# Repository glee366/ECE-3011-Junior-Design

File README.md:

# ECE-3011-Junior-Design
Junior Design project

https://github.com/Ian-Boraks/ECE3011-STEAM/tree/Feedback

# About This Project

## 📚 Educational Gameboy using ESP32

This project showcases an **educational Gameboy** designed using the ESP32 microcontroller. The Gameboy integrates various peripherals and features to provide an engaging learning experience for students, focusing on math and music skills. 

## Key Features
- **Microcontroller**: ESP32 for efficient processing and Wi-Fi capabilities.
- **Display**: A colorful LCD screen to render interactive content.
- **Input**: Capacitive touch buttons and a navigation switch for user interaction.
- **Feedback Mechanisms**: Integrated speakers and haptic feedback for immersive learning.

## Highlights in Code

### 1. Display Initialization
The following code snippet demonstrates how the LCD display was initialized to render the game's user interface:

```cpp
#include <TFT_eSPI.h>

TFT_eSPI tft = TFT_eSPI(); // Initialize TFT library

void setupDisplay() {
    tft.init();
    tft.setRotation(1);
    tft.fillScreen(TFT_BLACK);
    tft.setTextColor(TFT_WHITE, TFT_BLACK); // Set text color
    tft.setTextDatum(MC_DATUM); // Center alignment
}
```

### 2. Sound Feedback
Using the ESP32's PWM capabilities, the speaker plays sound effects based on user input:

```cpp
void playTone(int frequency, int duration) {
    ledcAttachPin(10, 0); // Attach GPIO 10 to channel 0
    ledcWriteTone(0, frequency); // Set frequency
    delay(duration);
    ledcWriteTone(0, 0); // Stop sound
}
```

### 3. Tap Detection with the Microphone
The microphone setup detects tap events for input recognition:

```cpp
void detectTap() {
    int soundLevel = analogRead(A0);
    if (soundLevel > THRESHOLD) {
        Serial.println("Tap detected!");
    }
}
```

## Repository Structure
```plaintext
├── code/
│   ├── src/
│   │   ├── main.cpp       # Main program logic
│   │   ├── display.cpp    # Display handling code
│   │   ├── sound.cpp      # Sound feedback logic
│   │   ├── input.cpp      # User input processing
│   └── assets/
│       ├── icons/         # Game icons
│       └── sounds/        # Sound effects
└── README.md              # Project documentation
```

## Product Image

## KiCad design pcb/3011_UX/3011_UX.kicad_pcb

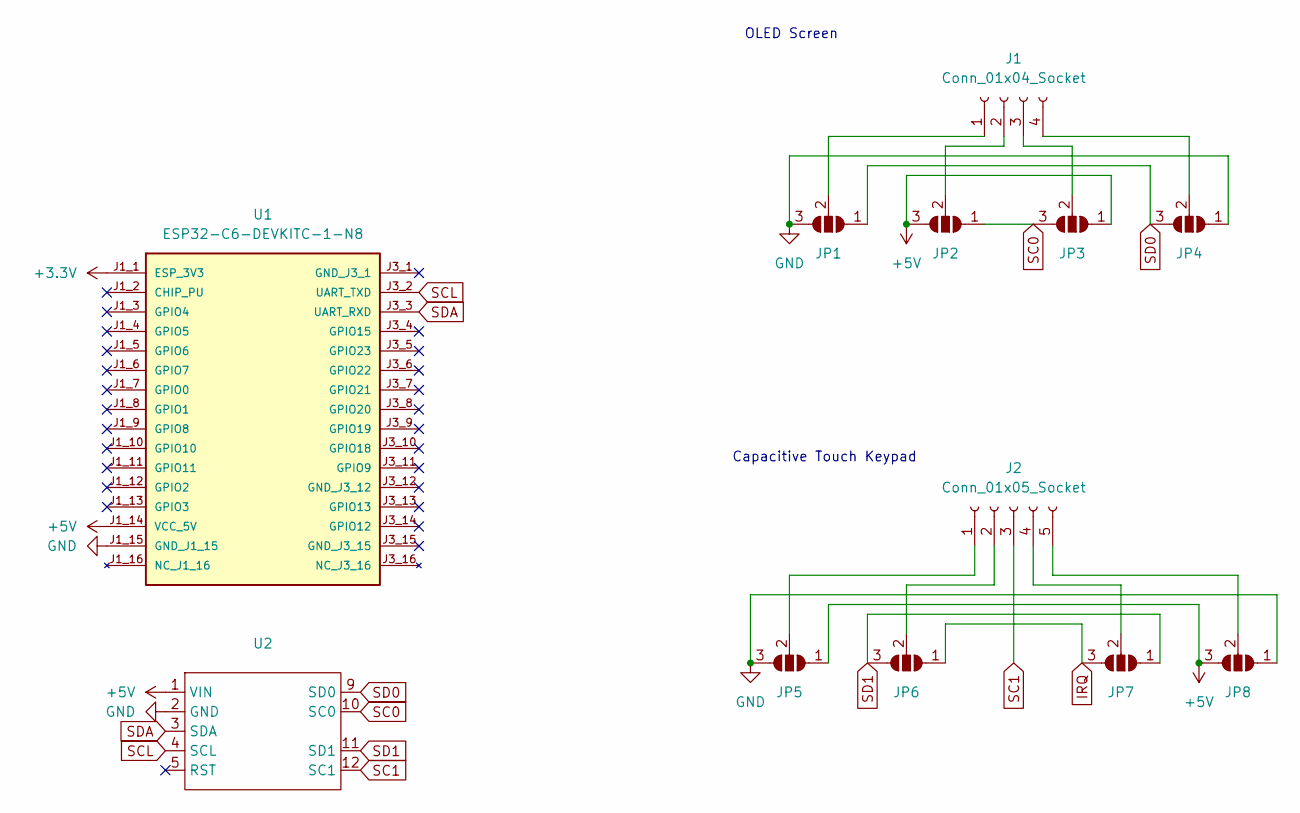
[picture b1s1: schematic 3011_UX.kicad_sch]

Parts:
J1: Conn_01x04_Socket; PinHeader_1x04_P2.54mm_Vertical
J2: Conn_01x05_Socket; PinHeader_1x05_P2.54mm_Vertical
JP1, JP2, JP3, JP4, JP5, JP6, JP7, JP8: SolderJumper_3_Open; SolderJumper-3_P1.3mm_Bridged2Bar12_RoundedPad1.0x1.5mm
U1: ESP32-C6-DEVKITC-1-N8; MODULE_ESP32-C6-DEVKITC-1-N8; PARTREV 1.3
U2: B0BFD4X6YV

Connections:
+3.3V: U1.J1_1 (ESP_3V3)
+5V: JP2.3 (B), JP3.1 (A), JP5.1 (A), JP8.3 (B), U1.J1_14 (VCC_5V), U2.1 (VIN)
GND: JP1.3 (B), JP4.1 (A), JP5.3 (B), JP8.1 (A), U1.J1_15 (GND_J1_15), U2.2 (GND)
IRQ: JP6.1 (A), JP7.3 (B)
unnamed: J1.1, JP1.2 (C)
unnamed: J1.2, JP2.2 (C)
unnamed: J1.3, JP3.2 (C)
unnamed: J1.4, JP4.2 (C)
unnamed: J2.1, JP5.2 (C)
unnamed: J2.2, JP6.2 (C)
unnamed: J2.4, JP7.2 (C)
unnamed: J2.5, JP8.2 (C)
RST: U2.5 (RST)
SC0: JP2.1 (A), JP3.3 (B), U2.10 (SC0)
SC1: J2.3, U2.12 (SC1)
SCL: U1.J3_2 (UART_TXD), U2.4 (SCL)
SD0: JP1.1 (A), JP4.3 (B), U2.9 (SD0)
SD1: JP6.3 (B), JP7.1 (A), U2.11 (SD1)
SDA: U1.J3_3 (UART_RXD), U2.3 (SDA)

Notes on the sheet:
OLED Screen
Capacitive Touch Keypad

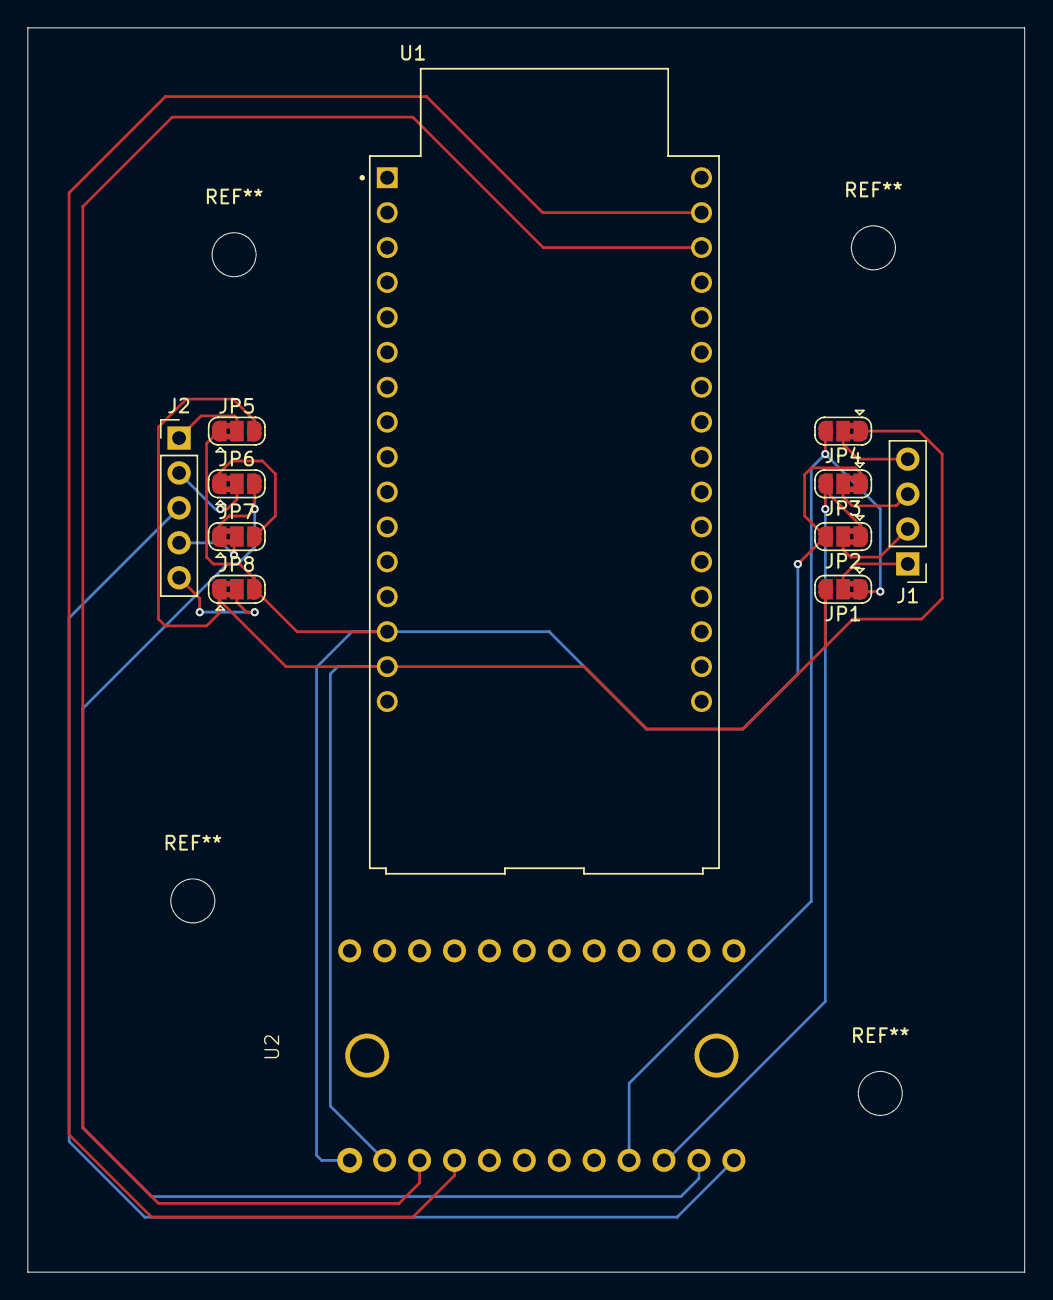
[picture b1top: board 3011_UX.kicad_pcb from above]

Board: 2 copper layers, 72.5 x 90.5 mm, 12 parts (0 on the bottom side), 17 nets.
